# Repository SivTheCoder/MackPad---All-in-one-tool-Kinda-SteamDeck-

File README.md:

# MackPad — All-in-One Macro Controller  
### By Sivansh Gupta  

---

##  Overview  
**MackPad** is a compact, high-efficiency macropad built to maximize functionality within minimal hardware constraints. Powered by the **Seeeduino XIAO ESP32-S3**, it leverages nearly every available GPIO pin to deliver a rich, customizable user experience.

Designed for **developers, creators, and productivity enthusiasts**, MackPad combines tactile input, visual feedback, and programmable workflows into a single portable device.

---

##  Project Showcase  

### Full Assembly (PCB + Case)

### PCB Design  

### Different Components  

##  Key Features  

- 3×3 NKRO Mechanical Keypad  
- Rotary Encoder with Push Functionality  
- 0.91" OLED Display (Real-time UI Feedback)  
- Neopixel RGB Backlighting  
- Hot-swappable Switch Support  
- Fully Programmable via KMK Firmware  
- Compact and Efficient Embedded Design  

---

##  Motivation  

MackPad began as a simple rotary encoder-based volume controller. It evolved into a fully-featured macropad focused on:

- Speeding up workflows  
- Reducing repetitive actions  
- Providing intuitive visual feedback  
- Maximizing functionality within hardware constraints  

---

##  Hardware Architecture  

- **Microcontroller:** Seeeduino XIAO ESP32-S3  
- **Input System:** 3×3 matrix with diodes (NKRO support)  
- **Rotary Encoder:** Analog-based custom decoding  
- **Display:** SSD1306 OLED (I2C, 128×32)  
- **Lighting:** WS2812 Neopixels  
- **Switches:** MX-style (hot-swappable with Kailh sockets)  

---

##  Firmware  

- Built using **KMK Firmware (CircuitPython)**  
- Features include:  
  - Custom keymaps and macros  
  - OLED UI (layer status, icons, system info)  
  - Rotary encoder multi-function control  
  - Neopixel-based visual feedback  
  - Custom key objects and advanced macro handling  

---

##  Usage  

### Setup  

1. Flash CircuitPython firmware onto the XIAO ESP32-S3  
2. Copy the following to the device:  
   - `code.py`  
   - Required KMK libraries  
   - Display assets (icons/images)  
3. Reboot the device  

---

### Customization  

All customization is handled inside `code.py`:

- Key mappings  
- Macros and shortcuts  
- RGB lighting behavior  
- OLED display output  

---

##  Bill of Materials (BOM)  

| Qty | Component                     | Notes               | USD   | INR   |
|-----|------------------------------|---------------------|-------|-------|
| 1   | Seeeduino XIAO ESP32-S3      | Microcontroller     | $6.00 | ₹500  |
| 9   | MX-style switches            | Mechanical switches | $4.50 | ₹375  |
| 9   | 1N4148 diodes                | Matrix diodes       | $0.90 | ₹75   |
| 1   | SSD1306 OLED (0.91", 128x32) | Display             | $3.00 | ₹250  |
| 9   | DSA keycaps                  | Keycaps             | $5.00 | ₹400  |
| 1   | Female header (1x4)          | Display mount       | $0.50 | ₹40   |
| 1   | EC11 rotary encoder          | Input control       | $1.50 | ₹120  |
| 3   | Resistors (10k, 47k, 100k)   | Voltage divider     | $0.30 | ₹30   |
| 9   | Kailh hot-swap sockets       | Switch mounting     | $6.00 | ₹500  |

### Estimated Total  
- **USD:** ~$27.70  
- **INR:** ~₹2,290  

*Prices may vary depending on supplier.*

---

##  Future Improvements  

### Advanced RGB System  
- Per-key RGB lighting  
- Layer-based color profiles  
- Reactive lighting effects  

### Touch Input Integration  
- Capacitive touch gestures  
- Swipe and tap controls  
- Hybrid input system  

### Wireless Capability  
- Bluetooth connectivity  
- Battery-powered operation  

### Enhanced UI  
- Animated OLED interface  
- Menu-based navigation  
- Dynamic macro previews  

---

##  Project Highlights  

- Efficient use of limited GPIO resources  
- Custom analog decoding for rotary encoder  
- Integration of hardware + firmware + UI design  
- Fully functional productivity tool  

---

### Custom Python-Based Companion Software (Steam Deck Integration)

- Development of a dedicated Python-based companion application designed to run alongside MackPad  
- Enables deep integration with devices like the Steam Deck or PC environments for advanced task execution  
- Supports bidirectional communication between MackPad and the host system (e.g., via Bluetooth/Wi-Fi/USB)  
- Allows dynamic macro triggering based on system context (active app, game state, or workflow)  
- Provides a customizable UI/dashboard for real-time control, monitoring, and macro management  
- Transforms MackPad from a standalone macropad into a hybrid hardware-software control system  
- Unlocks capabilities beyond traditional hackpads, including system-level automation, scripting, and adaptive workflows  

---

##  License  

This project is open-source and available under the MIT License.

---

##  Acknowledgements  

- KMK Firmware Community  
- Good people of Hack Club

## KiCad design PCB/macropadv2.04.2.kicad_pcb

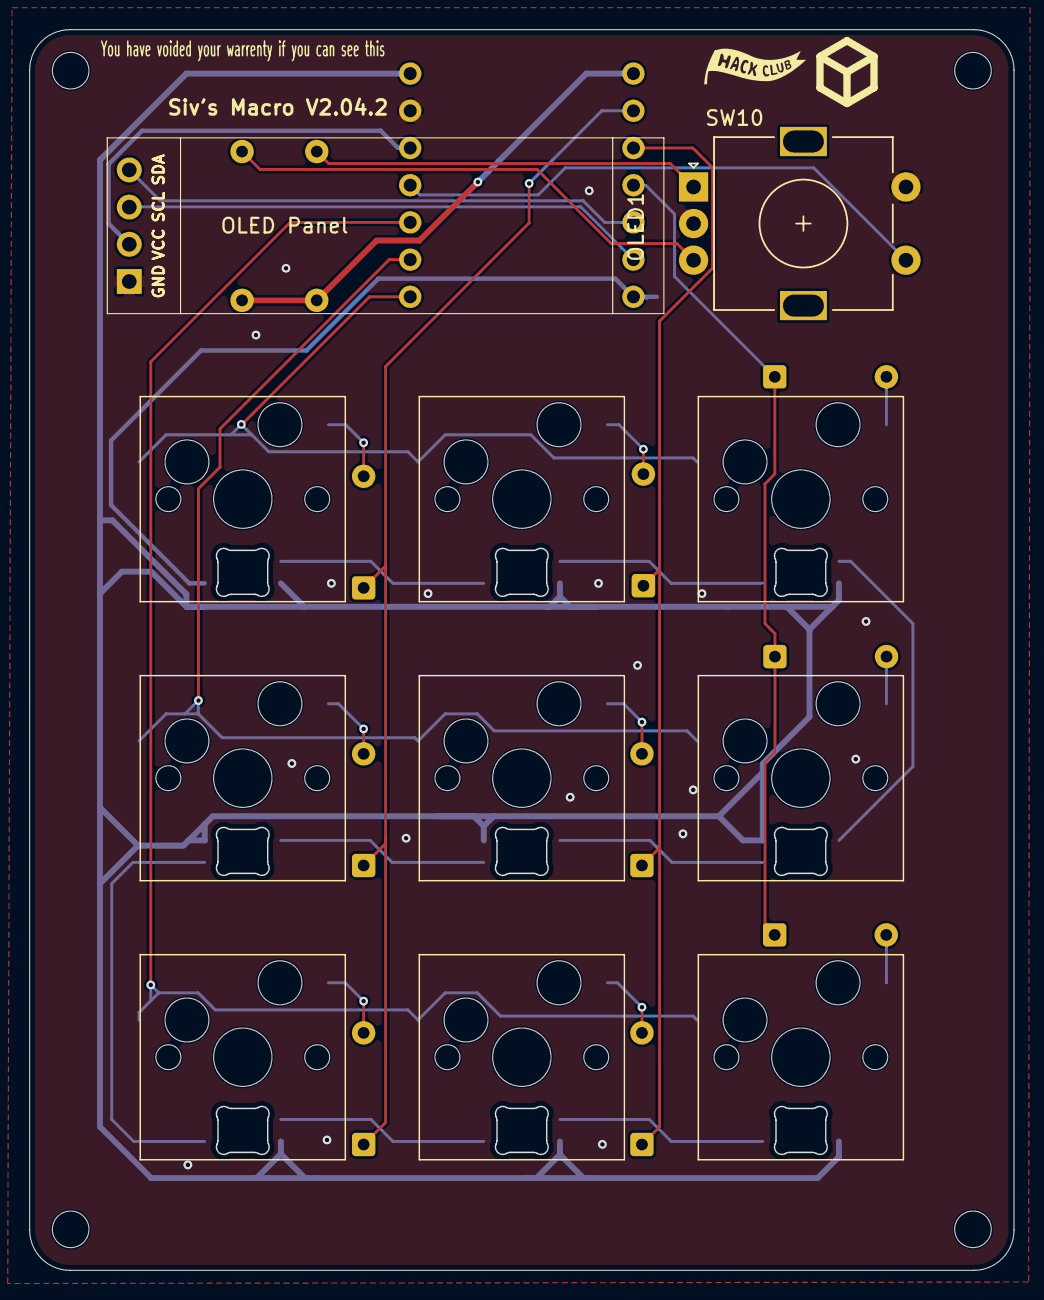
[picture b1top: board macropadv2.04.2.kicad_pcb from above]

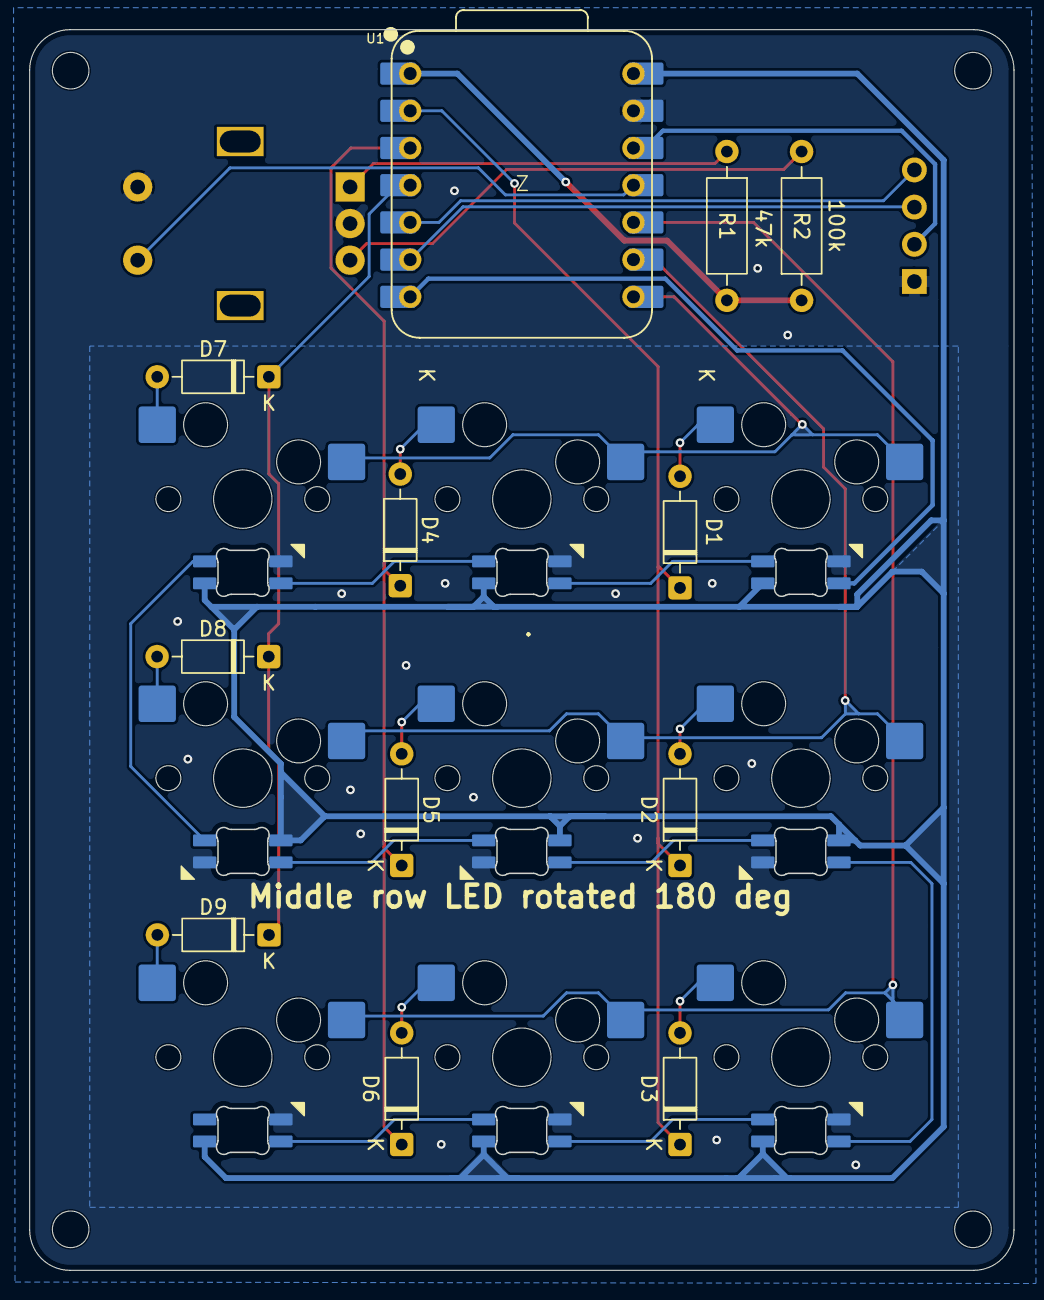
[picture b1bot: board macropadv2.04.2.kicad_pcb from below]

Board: 2 copper layers, 67.2 x 84.7 mm, 32 parts (21 on the bottom side), 33 nets.

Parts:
D1, D2, D3, D4, D5, D6, D7, D8, D9: 1N4148; D_DO-35_SOD27_P7.62mm_Horizontal
D10, D11, D12, D13, D14, D15, D16, D17, D18: SK6812MINI; MX_SK6812MINI-E_REV
OLED1: SSD1306-0.91-OLED-4pin-128x32
R1: 47k; R_Axial_DIN0207_L6.3mm_D2.5mm_P10.16mm_Horizontal
R2: 100k; R_Axial_DIN0207_L6.3mm_D2.5mm_P10.16mm_Horizontal
SW1, SW2, SW3, SW4, SW5, SW6, SW7, SW8, SW9: SW_Push; MX-Hotswap-1U
SW10: RotaryEncoder_Switch; RotaryEncoder_Alps_EC11E-Switch_Vertical_H20mm
U1: XIAO-RP2040-DIP

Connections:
+3V3: OLED1.2 (VCC), U1.12 (3V3)
+5V: D10.1 (VDD), D11.1 (VDD), D12.1 (VDD), D13.1 (VDD), D14.1 (VDD), D15.1 (VDD), D16.1 (VDD), D17.1 (VDD), D18.1 (VDD), U1.14 (VBUS)
A: R1.1, SW10.A
B: R2.2, SW10.B
C1: D1.1 (K), D2.1 (K), D3.1 (K), U1.2 (GPIO27/ADC1/A1)
C2: D4.1 (K), D5.1 (K), D6.1 (K), U1.3 (GPIO28/ADC2/A2)
C3: D7.1 (K), D8.1 (K), D9.1 (K), U1.4 (GPIO29/ADC3/A3)
GND: D10.3 (VSS), D11.3 (VSS), D12.3 (VSS), D13.3 (VSS), D14.3 (VSS), D15.3 (VSS), D16.3 (VSS), D17.3 (VSS), D18.3 (VSS), OLED1.1 (GND), SW10.C, SW10.S2, U1.13 (GND)
LED: D10.4 (DIN), U1.7 (GPIO0/TX)
unnamed: D1.2 (A), SW1.2
unnamed: D2.2 (A), SW2.2
unnamed: D3.2 (A), SW3.2
unnamed: D4.2 (A), SW4.2
unnamed: D5.2 (A), SW5.2
unnamed: D6.2 (A), SW6.2
unnamed: D7.2 (A), SW7.2
unnamed: D8.2 (A), SW8.2
unnamed: D9.2 (A), SW9.2
unnamed: D10.2 (DOUT), D11.4 (DIN)
unnamed: D11.2 (DOUT), D12.4 (DIN)
unnamed: D12.2 (DOUT), D13.4 (DIN)
unnamed: D13.2 (DOUT), D14.4 (DIN)
unnamed: D14.2 (DOUT), D15.4 (DIN)
unnamed: D15.2 (DOUT), D16.4 (DIN)
unnamed: D16.2 (DOUT), D17.4 (DIN)
unnamed: D17.2 (DOUT), D18.4 (DIN)
unnamed: OLED1.3 (SCL), U1.6 (GPIO7/SCL)
unnamed: OLED1.4 (SDA), U1.5 (GPIO6/SDA)
unnamed: SW10.S1, U1.11 (GPIO3/MOSI)
unnamed: R1.2, R2.1, U1.1 (GPIO26/ADC0/A0)
R1: SW1.1, SW4.1, SW7.1, U1.8 (GPIO1/RX)
R2: SW2.1, SW5.1, SW8.1, U1.9 (GPIO2/SCK)
R3: SW3.1, SW6.1, SW9.1, U1.10 (GPIO4/MISO)

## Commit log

2026-03-27 Remove hardware design and enclosure details from README
    Removed hardware design and enclosure sections from README.
2026-03-27 Update microcontroller from RP2040 to ESP32 S3
2026-03-30 Revise README for clarity and additional details
    Updated README to enhance clarity and structure, added project highlights and future improvements.
2026-03-30 Add new temporary image file
2026-03-30 Initialize Flask app with macro functionality
